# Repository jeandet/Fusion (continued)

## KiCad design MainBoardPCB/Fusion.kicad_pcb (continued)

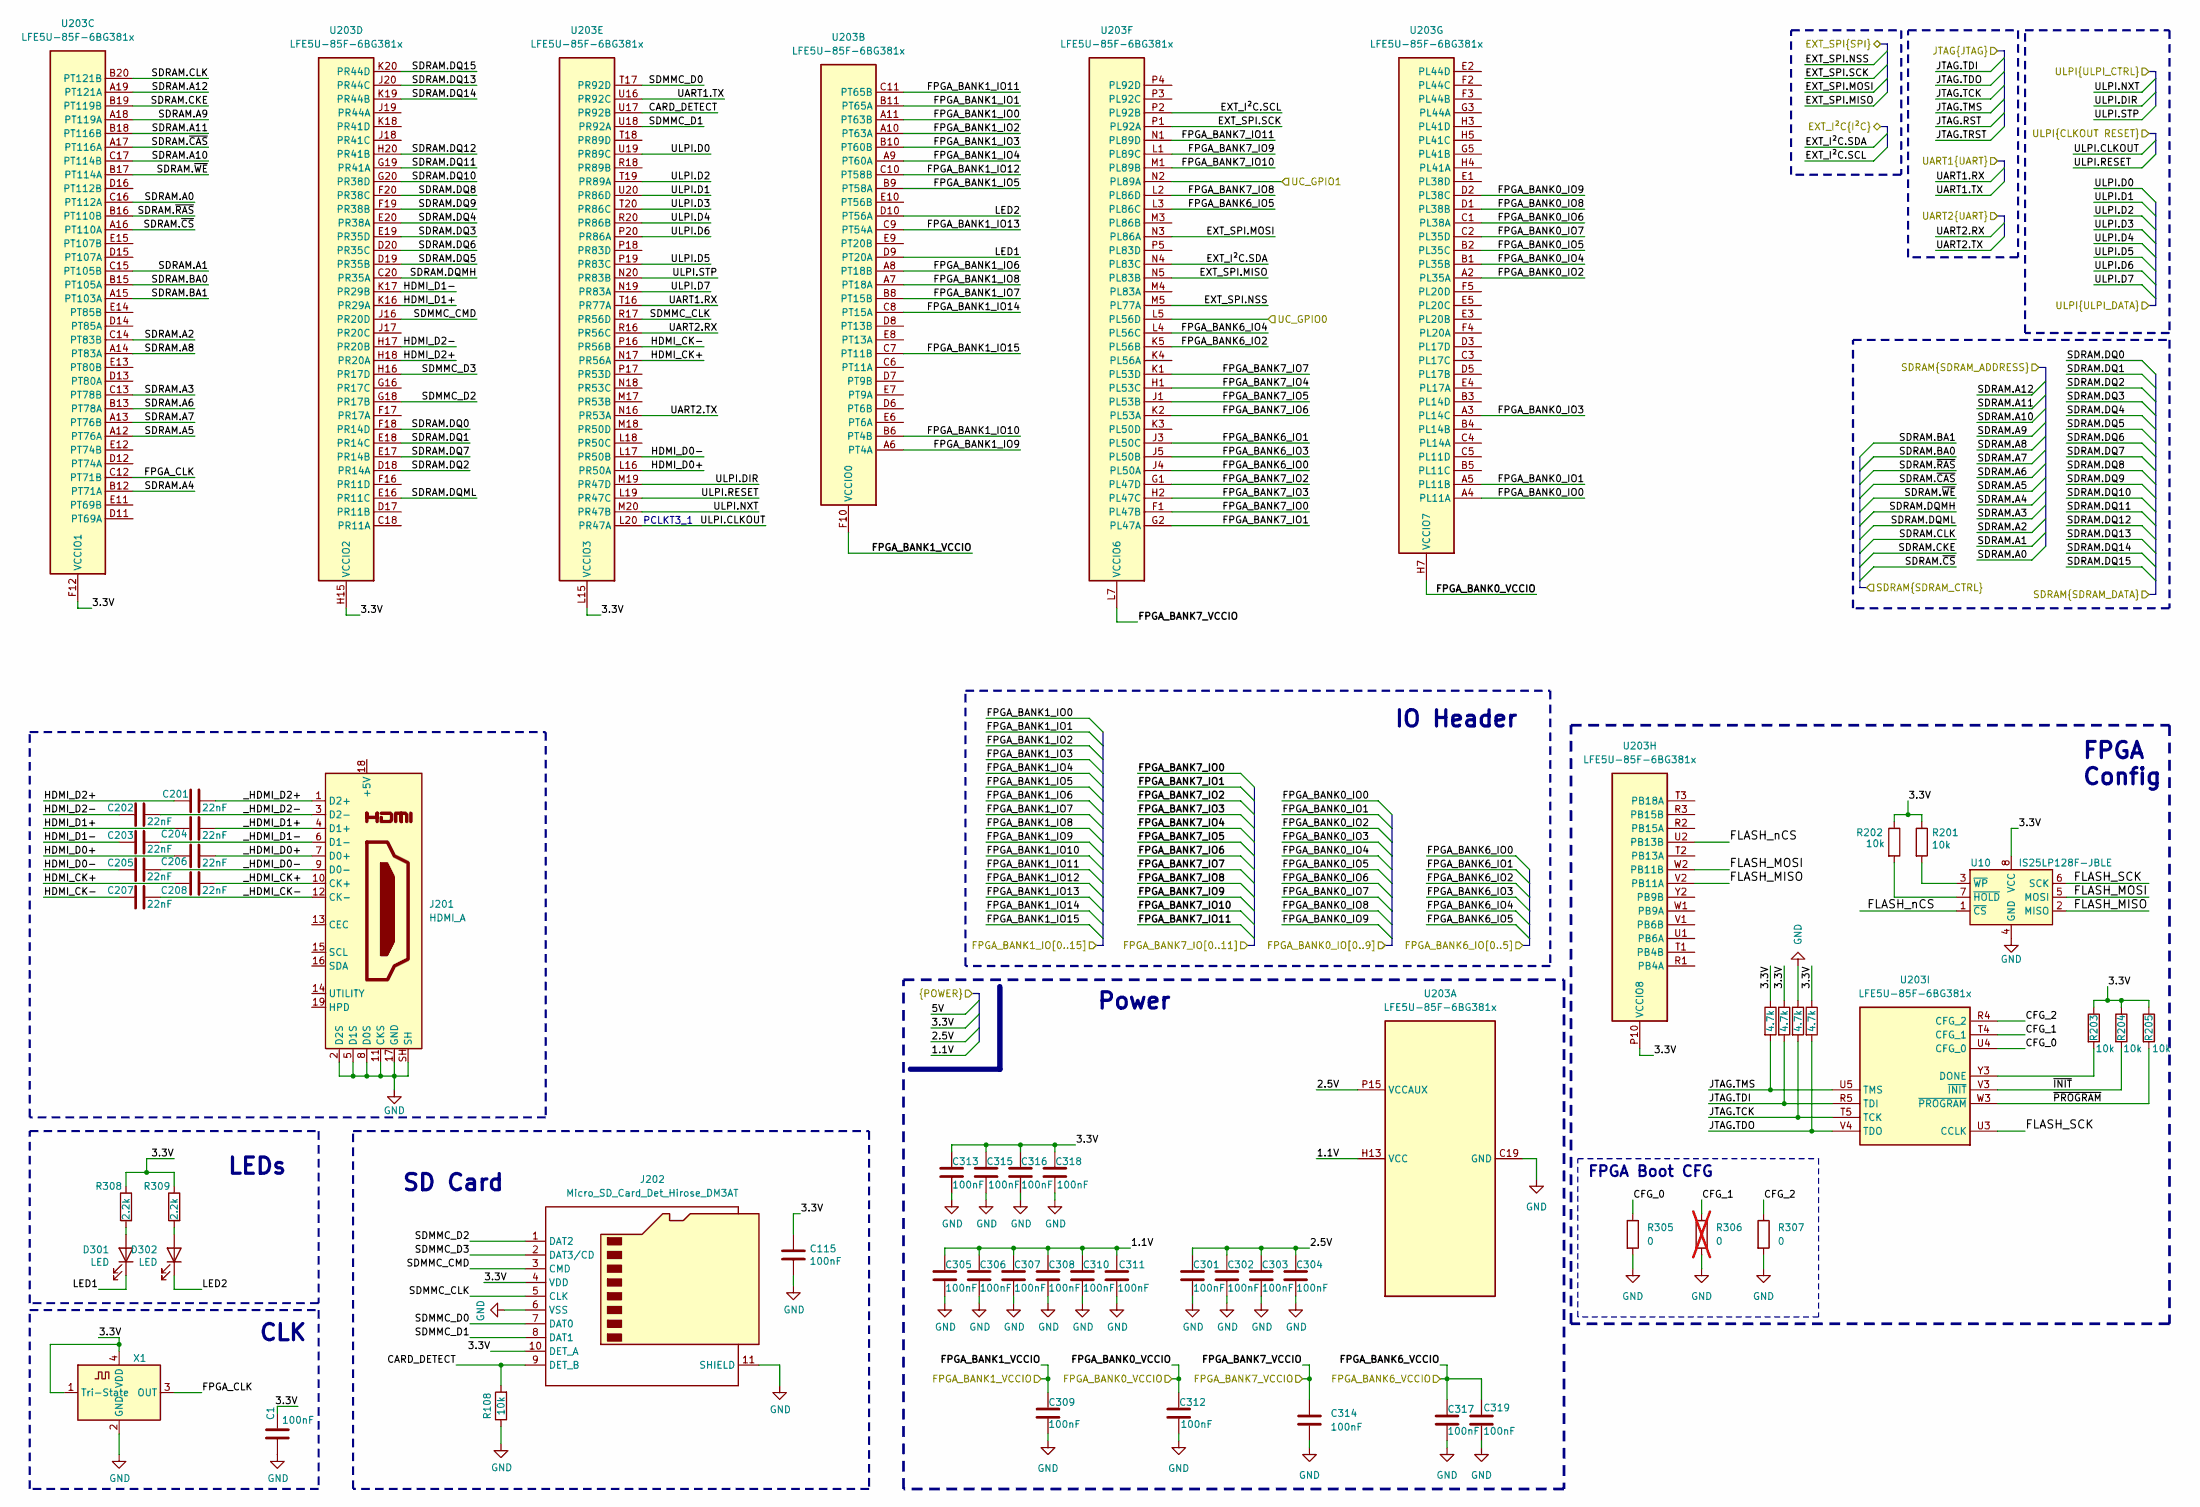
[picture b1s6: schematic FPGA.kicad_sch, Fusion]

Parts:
C1, C301, C302, C303, C304, C305, C306, C307, C308, C309, C310, C311, C312, C313, C314, C315, C316, C317, C318, C319: 100nF; C_0402_1005Metric_Pad0.74x0.62mm_HandSolder
C115: 100nF; C_0603_1608Metric_Pad1.08x0.95mm_HandSolder
C201, C202, C203, C204, C205, C206, C207, C208: 22nF; C_0402_1005Metric
D301, D302: LED; LED_0603_1608Metric_Pad1.05x0.95mm_HandSolder
J201: HDMI_A; HDMI_A_Molex_208658-1001_Horizontal
J202: Micro_SD_Card_Det_Hirose_DM3AT; microSD_HC_Hirose_DM3AT-SF-PEJM5
R108, R201, R202, R203, R204, R205: 10k; R_0402_1005Metric_Pad0.72x0.64mm_HandSolder
R301, R302, R303, R304: 4.7k; R_0402_1005Metric_Pad0.72x0.64mm_HandSolder
R305, R307: 0; R_0402_1005Metric_Pad0.72x0.64mm_HandSolder
R306: 0; R_0402_1005Metric_Pad0.72x0.64mm_HandSolder; not fitted
R308, R309: 2.2k; R_0402_1005Metric_Pad0.72x0.64mm_HandSolder
U10: IS25LP128F-JBLE; SOIC-8_5.3x5.3mm_P1.27mm; MPN IS25LP128F-JBLE; Mouser 454-W25Q128JVSIMTR
U203: LFE5U-85F-6BG381x; Lattice_caBGA-381_17x17mm_Layout20x20_P0.8mm
X1: ECS-2520MV-xxx-xx; Oscillator_SMD_ECS_2520MV-xxx-xx-4Pin_2.5x2.0mm

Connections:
/EXT_SPI_MISO: U203.N5 (PL83B); also elsewhere on the board
/EXT_SPI_MOSI: U203.N3 (PL86A); also elsewhere on the board
/EXT_SPI_NSS: U203.M5 (PL77A); also elsewhere on the board
/EXT_SPI_SCK: U203.P1 (PL92A); also elsewhere on the board
/FPGA/1.1V: C305.1, C306.1, C307.1, C308.1, C310.1, C311.1, U203.H8 (VCC), U203.H9 (VCC), U203.H10 (VCC), U203.H11 (VCC), U203.H12 (VCC), U203.H13 (VCC), U203.J8 (VCC), U203.J13 (VCC), U203.K8 (VCC), U203.K13 (VCC), U203.L8 (VCC), U203.L13 (VCC), U203.M8 (VCC), U203.M13 (VCC), U203.N8 (VCC), U203.N9 (VCC), U203.N10 (VCC), U203.N11 (VCC), U203.N12 (VCC), U203.N13 (VCC); also elsewhere on the board
/FPGA/2.5V: C301.1, C302.1, C303.1, C304.1, U203.F6 (VCCAUX), U203.F15 (VCCAUX), U203.P6 (VCCAUX), U203.P15 (VCCAUX); also elsewhere on the board
/FPGA/3.3V: C1.1, C115.1, C313.1, C315.1, C316.1, C317.1, C318.1, C319.1, J202.4 (VDD), J202.10 (DET_A), R201.1, R202.1, R203.1, R204.1, R205.1, R301.1, R303.1, R304.1, R308.1, R309.1, U10.8 (VCC), U203.F11 (VCCIO1), U203.F12 (VCCIO1), U203.H14 (VCCIO2), U203.H15 (VCCIO2), U203.J15 (VCCIO2), U203.L14 (VCCIO3), U203.L15 (VCCIO3), U203.M15 (VCCIO3), U203.P9 (VCCIO8), U203.P10 (VCCIO8), X1.1 (Tri-State), X1.4 (VDD); also elsewhere on the board
/FPGA/CARD_DETECT: J202.9 (DET_B), R108.2, U203.U17 (PR92B)
/FPGA/CFG_0: R305.1, U203.U4 (CFG_0)
/FPGA/CFG_1: R306.1, U203.T4 (CFG_1)
/FPGA/CFG_2: R307.1, U203.R4 (CFG_2)
/FPGA/FLASH_MISO: U10.2 (MISO), U203.V2 (PB11A)
/FPGA/FLASH_MOSI: U10.5 (MOSI), U203.W2 (PB11B)
/FPGA/FLASH_SCK: U10.6 (SCK), U203.U3 (CCLK)
/FPGA/FLASH_nCS: U10.1 (~CS), U203.U2 (PB13B)
/FPGA/FPGA_CLK: U203.C12 (PT71B), X1.3 (OUT)
/FPGA/HDMI_CK+: C208.1, U203.N17 (PR56A)
/FPGA/HDMI_CK-: C207.1, U203.P16 (PR56B)
/FPGA/HDMI_D0+: C206.1, U203.L16 (PR50A)
/FPGA/HDMI_D0-: C205.1, U203.L17 (PR50B)
/FPGA/HDMI_D1+: C204.1, U203.K16 (PR29A)
/FPGA/HDMI_D1-: C203.1, U203.K17 (PR29B)
/FPGA/HDMI_D2+: C201.1, U203.H18 (PR20A)
/FPGA/HDMI_D2-: C202.1, U203.H17 (PR20B)
/FPGA/JTAG.TCK: R302.2, U203.T5 (TCK); also elsewhere on the board
/FPGA/JTAG.TDI: R303.2, U203.R5 (TDI); also elsewhere on the board
/FPGA/JTAG.TDO: R301.2, U203.V4 (TDO); also elsewhere on the board
/FPGA/JTAG.TMS: R304.2, U203.U5 (TMS); also elsewhere on the board
/FPGA/LED1: D301.1 (K), U203.D9 (PT20A)
/FPGA/LED2: D302.1 (K), U203.D10 (PT56A)
/FPGA/SDMMC_CLK: J202.5 (CLK), U203.R17 (PR56D)
/FPGA/SDMMC_CMD: J202.3 (CMD), U203.J16 (PR20D)
/FPGA/SDMMC_D0: J202.7 (DAT0), U203.T17 (PR92D)
/FPGA/SDMMC_D1: J202.8 (DAT1), U203.U18 (PR92A)
/FPGA/SDMMC_D2: J202.1 (DAT2), U203.G18 (PR17B)
/FPGA/SDMMC_D3: J202.2 (DAT3/CD), U203.H16 (PR17D)
/FPGA/SDRAM.A0: U203.C16 (PT112A); also elsewhere on the board
/FPGA/SDRAM.A1: U203.C15 (PT105B); also elsewhere on the board
/FPGA/SDRAM.A2: U203.C14 (PT83B); also elsewhere on the board
/FPGA/SDRAM.A3: U203.C13 (PT78B); also elsewhere on the board
/FPGA/SDRAM.A4: U203.B12 (PT71A); also elsewhere on the board
/FPGA/SDRAM.A5: U203.A12 (PT76A); also elsewhere on the board
/FPGA/SDRAM.A6: U203.B13 (PT78A); also elsewhere on the board
/FPGA/SDRAM.A7: U203.A13 (PT76B); also elsewhere on the board
/FPGA/SDRAM.A8: U203.A14 (PT83A); also elsewhere on the board
/FPGA/SDRAM.A9: U203.A18 (PT119A); also elsewhere on the board
/FPGA/SDRAM.A10: U203.C17 (PT114B); also elsewhere on the board
/FPGA/SDRAM.A11: U203.B18 (PT116B); also elsewhere on the board
/FPGA/SDRAM.A12: U203.A19 (PT121A); also elsewhere on the board
/FPGA/SDRAM.BA0: U203.B15 (PT105A); also elsewhere on the board
/FPGA/SDRAM.BA1: U203.A15 (PT103A); also elsewhere on the board
/FPGA/SDRAM.CKE: U203.B19 (PT119B); also elsewhere on the board
/FPGA/SDRAM.CLK: U203.B20 (PT121B); also elsewhere on the board
/FPGA/SDRAM.DQ0: U203.F18 (PR14D); also elsewhere on the board
/FPGA/SDRAM.DQ1: U203.E18 (PR14C); also elsewhere on the board
/FPGA/SDRAM.DQ2: U203.D18 (PR14A); also elsewhere on the board
/FPGA/SDRAM.DQ3: U203.E19 (PR35D); also elsewhere on the board
/FPGA/SDRAM.DQ4: U203.E20 (PR38A); also elsewhere on the board
/FPGA/SDRAM.DQ5: U203.D19 (PR35B); also elsewhere on the board
/FPGA/SDRAM.DQ6: U203.D20 (PR35C); also elsewhere on the board
/FPGA/SDRAM.DQ7: U203.E17 (PR14B); also elsewhere on the board
/FPGA/SDRAM.DQ8: U203.F20 (PR38C); also elsewhere on the board
/FPGA/SDRAM.DQ9: U203.F19 (PR38B); also elsewhere on the board
/FPGA/SDRAM.DQ10: U203.G20 (PR38D); also elsewhere on the board
/FPGA/SDRAM.DQ11: U203.G19 (PR41A); also elsewhere on the board
/FPGA/SDRAM.DQ12: U203.H20 (PR41B); also elsewhere on the board
/FPGA/SDRAM.DQ13: U203.J20 (PR44C); also elsewhere on the board
/FPGA/SDRAM.DQ14: U203.K19 (PR44B); also elsewhere on the board
/FPGA/SDRAM.DQ15: U203.K20 (PR44D); also elsewhere on the board
/FPGA/SDRAM.DQMH: U203.C20 (PR35A); also elsewhere on the board
/FPGA/SDRAM.DQML: U203.E16 (PR11C); also elsewhere on the board
/FPGA/SDRAM.~CAS: U203.A17 (PT116A); also elsewhere on the board
/FPGA/SDRAM.~CS: U203.A16 (PT110A); also elsewhere on the board
/FPGA/SDRAM.~RAS: U203.B16 (PT110B); also elsewhere on the board
/FPGA/SDRAM.~WE: U203.B17 (PT114A); also elsewhere on the board
/FPGA/UART1.RX: U203.T16 (PR77A); also elsewhere on the board
/FPGA/UART1.TX: U203.U16 (PR92C); also elsewhere on the board
/FPGA/UART2.RX: U203.R16 (PR56C); also elsewhere on the board
/FPGA/UART2.TX: U203.N16 (PR53A); also elsewhere on the board
/FPGA/ULPI.CLKOUT: U203.L20 (PR47A); also elsewhere on the board
/FPGA/ULPI.D0: U203.U19 (PR89C); also elsewhere on the board
/FPGA/ULPI.D1: U203.U20 (PR86D); also elsewhere on the board
/FPGA/ULPI.D2: U203.T19 (PR89A); also elsewhere on the board
/FPGA/ULPI.D3: U203.T20 (PR86C); also elsewhere on the board
/FPGA/ULPI.D4: U203.R20 (PR86B); also elsewhere on the board
/FPGA/ULPI.D5: U203.P19 (PR83C); also elsewhere on the board
/FPGA/ULPI.D6: U203.P20 (PR86A); also elsewhere on the board
/FPGA/ULPI.D7: U203.N19 (PR83A); also elsewhere on the board
/FPGA/ULPI.DIR: U203.M19 (PR47D); also elsewhere on the board
/FPGA/ULPI.NXT: U203.M20 (PR47B); also elsewhere on the board
/FPGA/ULPI.RESET: U203.L19 (PR47C); also elsewhere on the board
/FPGA/ULPI.STP: U203.N20 (PR83B); also elsewhere on the board
/FPGA/_HDMI_CK+: C208.2, J201.10 (CK+)
/FPGA/_HDMI_CK-: C207.2, J201.12 (CK-)
/FPGA/_HDMI_D0+: C206.2, J201.7 (D0+)
/FPGA/_HDMI_D0-: C205.2, J201.9 (D0-)
/FPGA/_HDMI_D1+: C204.2, J201.4 (D1+)
/FPGA/_HDMI_D1-: C203.2, J201.6 (D1-)
/FPGA/_HDMI_D2+: C201.2, J201.1 (D2+)
/FPGA/_HDMI_D2-: C202.2, J201.3 (D2-)
/FPGA/~INIT: R204.2, U203.V3 (~INIT)
/FPGA/~PROGRAM: R205.2, U203.W3 (~PROGRAM)
/FPGA_BANK0_IO0: U203.A4 (PL11A); also elsewhere on the board
/FPGA_BANK0_IO1: U203.A5 (PL11B); also elsewhere on the board
/FPGA_BANK0_IO2: U203.A2 (PL35A); also elsewhere on the board
/FPGA_BANK0_IO3: U203.A3 (PL14C); also elsewhere on the board
/FPGA_BANK0_IO4: U203.B1 (PL35B); also elsewhere on the board
/FPGA_BANK0_IO5: U203.B2 (PL35C); also elsewhere on the board
/FPGA_BANK0_IO6: U203.C1 (PL38A); also elsewhere on the board
/FPGA_BANK0_IO7: U203.C2 (PL35D); also elsewhere on the board
/FPGA_BANK0_IO8: U203.D1 (PL38B); also elsewhere on the board
/FPGA_BANK0_IO9: U203.D2 (PL38C); also elsewhere on the board
/FPGA_BANK0_VCCIO: C312.1, U203.H6 (VCCIO7), U203.H7 (VCCIO7), U203.J6 (VCCIO7); also elsewhere on the board
/FPGA_BANK1_IO0: U203.A11 (PT63B); also elsewhere on the board
/FPGA_BANK1_IO1: U203.B11 (PT65A); also elsewhere on the board
/FPGA_BANK1_IO2: U203.A10 (PT63A); also elsewhere on the board
/FPGA_BANK1_IO3: U203.B10 (PT60B); also elsewhere on the board
/FPGA_BANK1_IO4: U203.A9 (PT60A); also elsewhere on the board
/FPGA_BANK1_IO5: U203.B9 (PT58A); also elsewhere on the board
/FPGA_BANK1_IO6: U203.A8 (PT18B); also elsewhere on the board
/FPGA_BANK1_IO7: U203.B8 (PT15B); also elsewhere on the board
/FPGA_BANK1_IO8: U203.A7 (PT18A); also elsewhere on the board
/FPGA_BANK1_IO9: U203.A6 (PT4A); also elsewhere on the board
/FPGA_BANK1_IO10: U203.B6 (PT4B); also elsewhere on the board
/FPGA_BANK1_IO11: U203.C11 (PT65B); also elsewhere on the board
/FPGA_BANK1_IO12: U203.C10 (PT58B); also elsewhere on the board
/FPGA_BANK1_IO13: U203.C9 (PT54A); also elsewhere on the board
/FPGA_BANK1_IO14: U203.C8 (PT15A); also elsewhere on the board
/FPGA_BANK1_IO15: U203.C7 (PT11B); also elsewhere on the board
/FPGA_BANK1_VCCIO: C309.1, U203.F9 (VCCIO0), U203.F10 (VCCIO0); also elsewhere on the board
/FPGA_BANK6_IO0: U203.J4 (PL50A); also elsewhere on the board
/FPGA_BANK6_IO1: U203.J3 (PL50C); also elsewhere on the board
/FPGA_BANK6_IO2: U203.K5 (PL56B); also elsewhere on the board
/FPGA_BANK6_IO3: U203.J5 (PL50B); also elsewhere on the board
/FPGA_BANK6_IO4: U203.L4 (PL56C); also elsewhere on the board
/FPGA_BANK6_IO5: U203.L3 (PL86C); also elsewhere on the board
/FPGA_BANK7_IO0: U203.F1 (PL47B); also elsewhere on the board
/FPGA_BANK7_IO1: U203.G2 (PL47A); also elsewhere on the board
/FPGA_BANK7_IO2: U203.G1 (PL47D); also elsewhere on the board
/FPGA_BANK7_IO3: U203.H2 (PL47C); also elsewhere on the board
/FPGA_BANK7_IO4: U203.H1 (PL53C); also elsewhere on the board
/FPGA_BANK7_IO5: U203.J1 (PL53B); also elsewhere on the board
/FPGA_BANK7_IO6: U203.K2 (PL53A); also elsewhere on the board
/FPGA_BANK7_IO7: U203.K1 (PL53D); also elsewhere on the board
/FPGA_BANK7_IO8: U203.L2 (PL86D); also elsewhere on the board
/FPGA_BANK7_IO9: U203.L1 (PL89C); also elsewhere on the board
/FPGA_BANK7_IO10: U203.M1 (PL89B); also elsewhere on the board
/FPGA_BANK7_IO11: U203.N1 (PL89D); also elsewhere on the board
/FPGA_BANK7_VCCIO: C314.1, U203.L6 (VCCIO6), U203.L7 (VCCIO6), U203.M6 (VCCIO6); also elsewhere on the board
/I2C1_SCL: U203.P2 (PL92B); also elsewhere on the board
/I2C1_SDA: U203.N4 (PL83C); also elsewhere on the board
/UC_GPIO0: U203.L5 (PL56D); also elsewhere on the board
/UC_GPIO1: U203.N2 (PL89A); also elsewhere on the board
GND: C1.2, C115.2, C301.2, C302.2, C303.2, C304.2, C305.2, C306.2, C307.2, C308.2, C309.2, C310.2, C311.2, C312.2, C313.2, C314.2, C315.2, C316.2, C317.2, C318.2, C319.2, J201.2 (D2S), J201.5 (D1S), J201.8 (D0S), J201.11 (CKS), J201.17 (GND), J201.SH, J202.6 (VSS), J202.11 (SHIELD), R108.1, R302.1, R305.2, R306.2, R307.2, U10.4 (GND), U203.B7 (GND), U203.B14 (GND), U203.C19 (GND), U203.D4 (GND), U203.F7 (GND), U203.F8 (GND), U203.F13 (GND), U203.F14 (GND), U203.G4 (GND), U203.G6 (GND), U203.G7 (GND), U203.G8 (GND), U203.G9 (GND), U203.G10 (GND), U203.G11 (GND), U203.G12 (GND), U203.G13 (GND), U203.G14 (GND), U203.G15 (GND), U203.G17 (GND), U203.H19 (GND), U203.J2 (GND), U203.J7 (GND), U203.J9 (GND), U203.J10 (GND), U203.J11 (GND), U203.J12 (GND), U203.J14 (GND), U203.K6 (GND), U203.K7 (GND), U203.K9 (GND), U203.K10 (GND), U203.K11 (GND), U203.K12 (GND), U203.K14 (GND), U203.K15 (GND), U203.L9 (GND), U203.L10 (GND), U203.L11 (GND), U203.L12 (GND), U203.M2 (GND), U203.M7 (GND), U203.M9 (GND), U203.M10 (GND), U203.M11 (GND), U203.M12 (GND), U203.M14 (GND), U203.M16 (GND), U203.N6 (GND), U203.N7 (GND), U203.N14 (GND), U203.N15 (GND), U203.P7 (GND), U203.P8 (GND), U203.P11 (GND), U203.P12 (GND), U203.P13 (GND), U203.P14 (GND), U203.R19 (GND), U203.T6 (GND), U203.T7 (GND), U203.T8 (GND), U203.T9 (GND), U203.T10 (GND), U203.T11 (GND), U203.T12 (GND), U203.T13 (GND), U203.T14 (GND), U203.T15 (GND), U203.U6 (GND), U203.U7 (GND), U203.U8 (GND), U203.U9 (GND), U203.U10 (GND), U203.U11 (GND), U203.U12 (GND), U203.U13 (GND), U203.U14 (GND), U203.U15 (GND), U203.V5 (GND), U203.V6 (GND), U203.V7 (GND), U203.V8 (GND), U203.V9 (GND), U203.V10 (GND), U203.V11 (GND), U203.V12 (GND), U203.V13 (GND), U203.V14 (GND), U203.V15 (GND), U203.V16 (GND), U203.V17 (GND), U203.V18 (GND), U203.V19 (GND), U203.V20 (GND), U203.W6 (GND), U203.W7 (GND), U203.W12 (GND), U203.W15 (GND), U203.W16 (GND), U203.W19 (GND), U203.W20 (GND), U203.Y5 (GND), U203.Y6 (GND), U203.Y7 (GND), U203.Y8 (GND), U203.Y11 (GND), U203.Y12 (GND), U203.Y14 (GND), U203.Y15 (GND), U203.Y16 (GND), U203.Y17 (GND), U203.Y19 (GND), X1.2 (GND); also elsewhere on the board
unnamed: D301.2 (A), R308.2
unnamed: D302.2 (A), R309.2
unnamed: R202.2, U10.7 (~HOLD)
unnamed: R201.2, U10.3 (~WP)
unnamed: R203.2, U203.Y3 (DONE)

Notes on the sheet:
FPGA Config
FPGA Boot CFG
LEDs
Power
CLK
PCLKT3_1
IO Header
SD Card

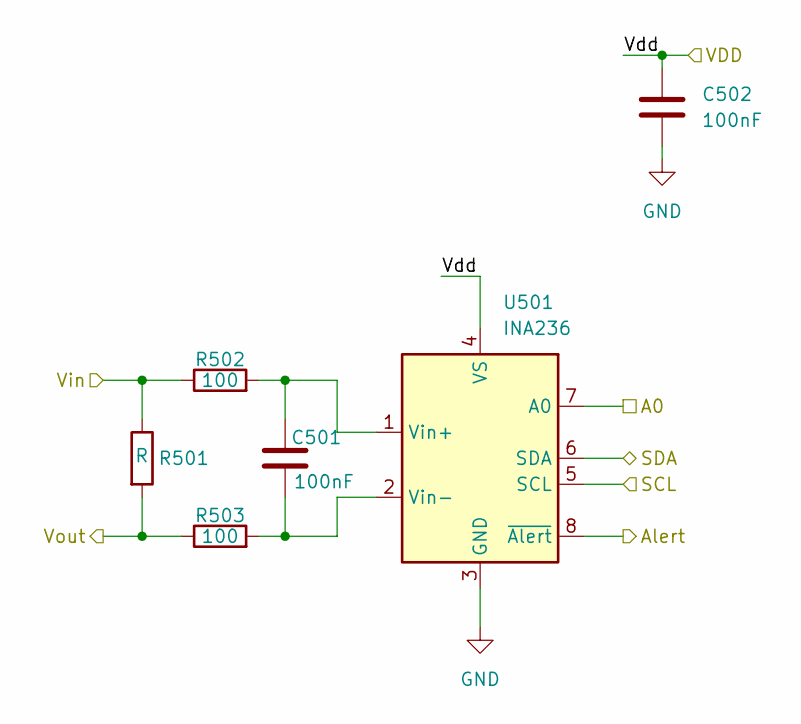
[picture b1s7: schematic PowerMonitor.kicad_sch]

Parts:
C501: 100nF; C_0402_1005Metric_Pad0.74x0.62mm_HandSolder
C502: 100nF; C_0603_1608Metric_Pad1.08x0.95mm_HandSolder
R501: R; R_1210_3225Metric_Pad1.30x2.65mm_HandSolder
R502, R503: 100; R_0402_1005Metric_Pad0.72x0.64mm_HandSolder
U501: INA236; SOT-23-8_Handsoldering

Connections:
/Alert: U501.8 (~Alert); also elsewhere on the board
/FPGA/3.3V: C502.1, R501.2, R503.1, U501.4 (VS); also elsewhere on the board
/JTAG/PSU.SCL: U501.5 (SCL); also elsewhere on the board
/JTAG/PSU.SDA: U501.6 (SDA); also elsewhere on the board
/Power/PowerMonitor1/Vin: R501.1, R502.1; also elsewhere on the board
GND: C502.2, U501.3 (GND), U501.7 (A0); also elsewhere on the board
unnamed: C501.1, R502.2, U501.1 (Vin+)
unnamed: C501.2, R503.2, U501.2 (Vin-)

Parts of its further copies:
C801, C901, C1001: 100nF; C_0402_1005Metric_Pad0.74x0.62mm_HandSolder
C802, C902, C1002: 100nF; C_0603_1608Metric_Pad1.08x0.95mm_HandSolder
R801, R901, R1001: R; R_1210_3225Metric_Pad1.30x2.65mm_HandSolder
R802, R803, R902, R903, R1002, R1003: 100; R_0402_1005Metric_Pad0.72x0.64mm_HandSolder
U801, U901, U1001: INA236; SOT-23-8_Handsoldering

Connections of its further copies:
/Alert: U801.8 (~Alert), U901.8 (~Alert), U1001.8 (~Alert); also elsewhere on the board
/FPGA/1.1V: R801.2, R803.1; also elsewhere on the board
/FPGA/2.5V: R901.2, R903.1; also elsewhere on the board
/FPGA/3.3V: C802.1, C902.1, C1002.1, U801.4 (VS), U801.7 (A0), U901.4 (VS), U1001.4 (VS); also elsewhere on the board
/FPGA/5V: R1001.2, R1003.1; also elsewhere on the board
/JTAG/PSU.SCL: U801.5 (SCL), U901.5 (SCL), U1001.5 (SCL), U1001.7 (A0); also elsewhere on the board
/JTAG/PSU.SDA: U801.6 (SDA), U901.6 (SDA), U901.7 (A0), U1001.6 (SDA); also elsewhere on the board
/Power/PowerMonitor2/Vin: R901.1, R902.1; also elsewhere on the board
/Power/PowerMonitor/Vin: R801.1, R802.1; also elsewhere on the board
/USB_5V: R1001.1, R1002.1; also elsewhere on the board
GND: C802.2, C902.2, C1002.2, U801.3 (GND), U901.3 (GND), U1001.3 (GND); also elsewhere on the board
unnamed: C801.1, R802.2, U801.1 (Vin+)
unnamed: C801.2, R803.2, U801.2 (Vin-)
unnamed: C901.1, R902.2, U901.1 (Vin+)
unnamed: C901.2, R903.2, U901.2 (Vin-)
unnamed: C1001.1, R1002.2, U1001.1 (Vin+)
unnamed: C1001.2, R1003.2, U1001.2 (Vin-)

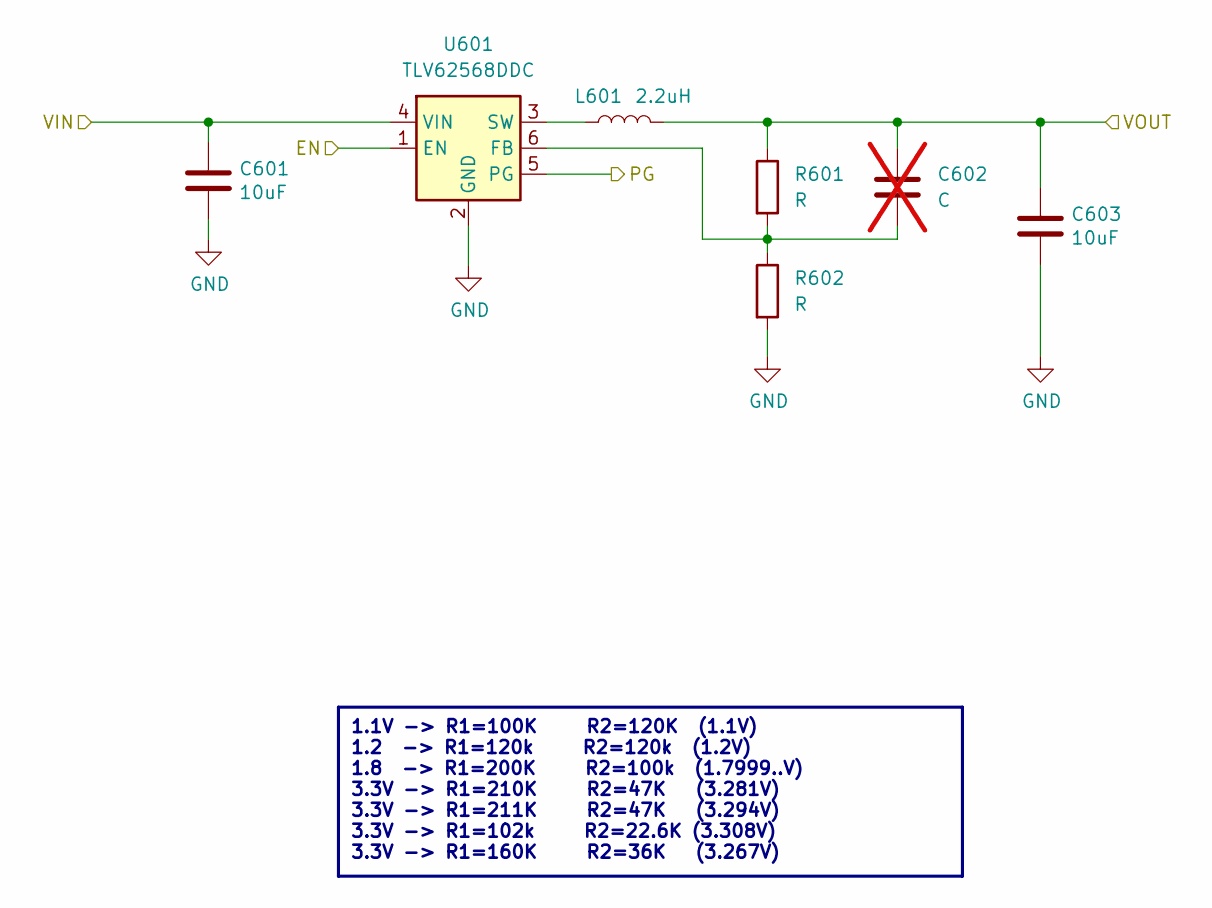
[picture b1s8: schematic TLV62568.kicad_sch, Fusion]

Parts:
C601, C603: 10uF; C_1206_3216Metric_Pad1.33x1.80mm_HandSolder
C602: C; C_0402_1005Metric_Pad0.74x0.62mm_HandSolder; not fitted
L601: 2.2uH; L_1206_3216Metric_Pad1.42x1.75mm_HandSolder
R601, R602: R; R_0402_1005Metric_Pad0.72x0.64mm_HandSolder
U601: TLV62568DDC; SOT-23-6

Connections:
/FPGA/5V: C601.1, U601.1 (EN), U601.4 (VIN); also elsewhere on the board
/Power/PowerMonitor1/Vin: C602.1, C603.1, L601.2, R601.1; also elsewhere on the board
/Power/TLV62568/PG: U601.5 (PG); also elsewhere on the board
GND: C601.2, C603.2, R602.2, U601.2 (GND); also elsewhere on the board
unnamed: C602.2, R601.2, R602.1, U601.6 (FB)
unnamed: L601.1, U601.3 (SW)

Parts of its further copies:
C701, C703: 10uF; C_1206_3216Metric_Pad1.33x1.80mm_HandSolder
C702: C; C_0402_1005Metric_Pad0.74x0.62mm_HandSolder; not fitted
L701: 2.2uH; L_1206_3216Metric_Pad1.42x1.75mm_HandSolder
R701, R702: R; R_0402_1005Metric_Pad0.72x0.64mm_HandSolder
U701: TLV62568DDC; SOT-23-6

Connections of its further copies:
/FPGA/5V: C701.1, U701.4 (VIN); also elsewhere on the board
/Power/PowerMonitor/Vin: C702.1, C703.1, L701.2, R701.1; also elsewhere on the board
/Power/TLV62568/PG: U701.1 (EN); also elsewhere on the board
/Power/TLV62569/PG: U701.5 (PG)
GND: C701.2, C703.2, R702.2, U701.2 (GND); also elsewhere on the board
unnamed: C702.2, R701.2, R702.1, U701.6 (FB)
unnamed: L701.1, U701.3 (SW)

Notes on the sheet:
1.1V -> R1=100K R2=120K (1.1V) 1.2 -> R1=120k R2=120k (1.2V) 1.8 -> R1=200K R2=100k (1.7999..V) 3.3V -> R1=210K R2=47K (3.281V) 3.3V -> R1=211K R2=47K (3.294V) 3.3V -> R1=102k R2=22.6K (3.308V) 3.3V -> R1=160K R2=36K (3.267V)

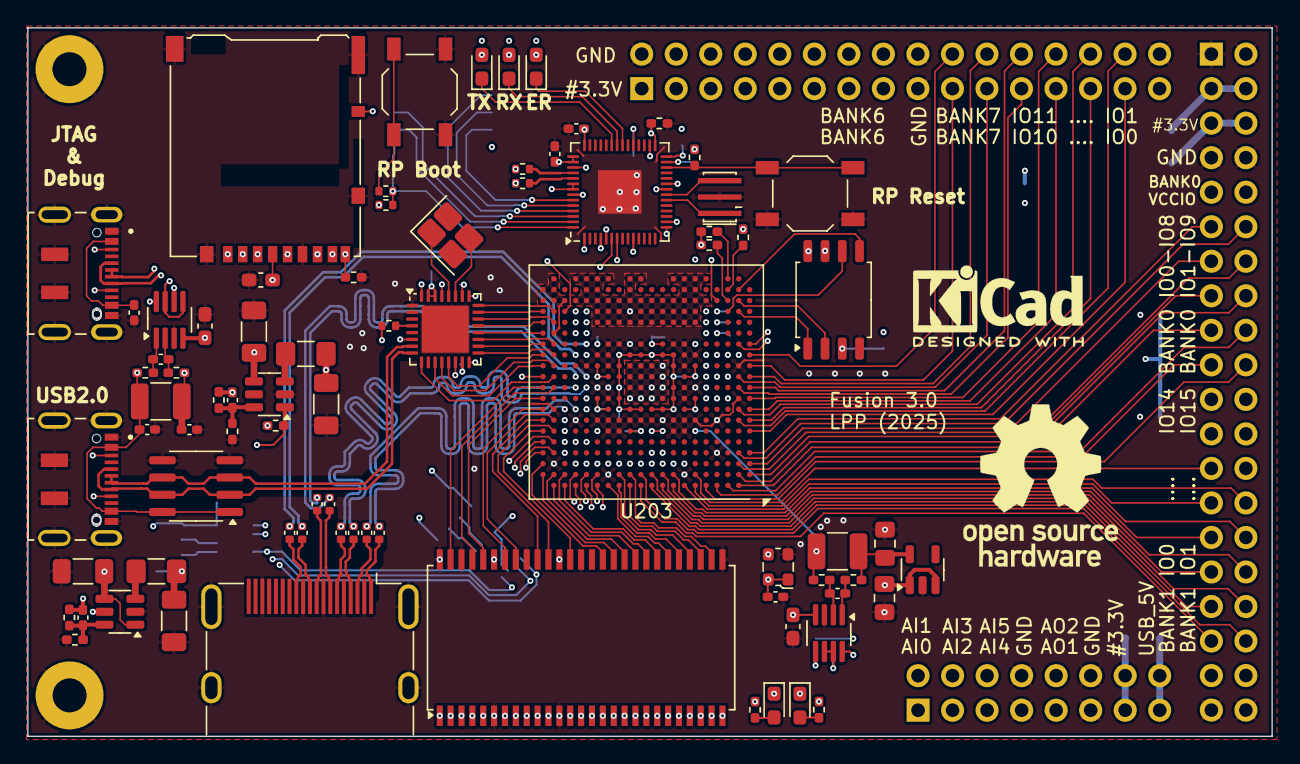
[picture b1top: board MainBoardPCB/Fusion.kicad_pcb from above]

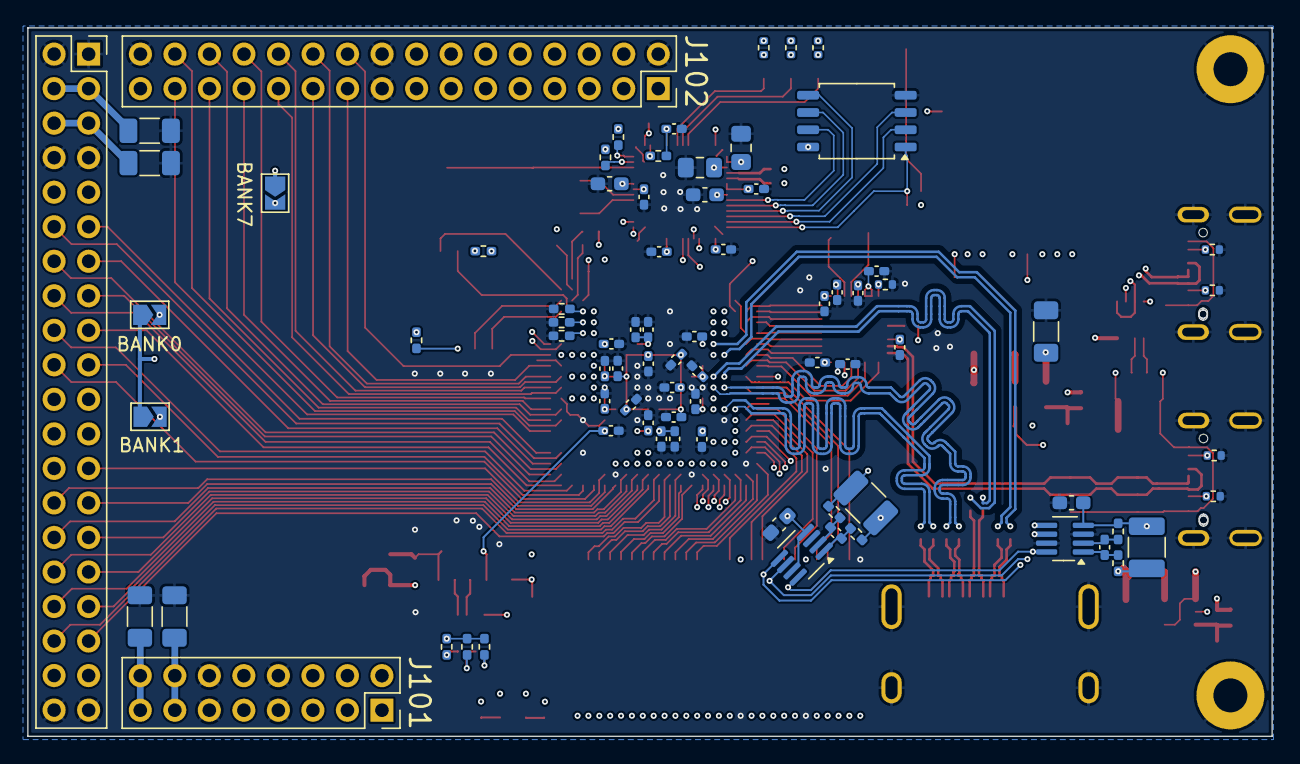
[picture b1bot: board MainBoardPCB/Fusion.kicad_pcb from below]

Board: 4 copper layers, 91.5 x 52.1 mm, 159 parts (78 on the bottom side), 214 nets.

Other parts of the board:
H101, H102: MountingHole_Pad; MountingHole_2.5mm_Pad
SYM101: Logo_Open_Hardware_Small; OSHW-Logo_11.4x12mm_SilkScreen

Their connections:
GND: H101.1, H102.1; also elsewhere on the board

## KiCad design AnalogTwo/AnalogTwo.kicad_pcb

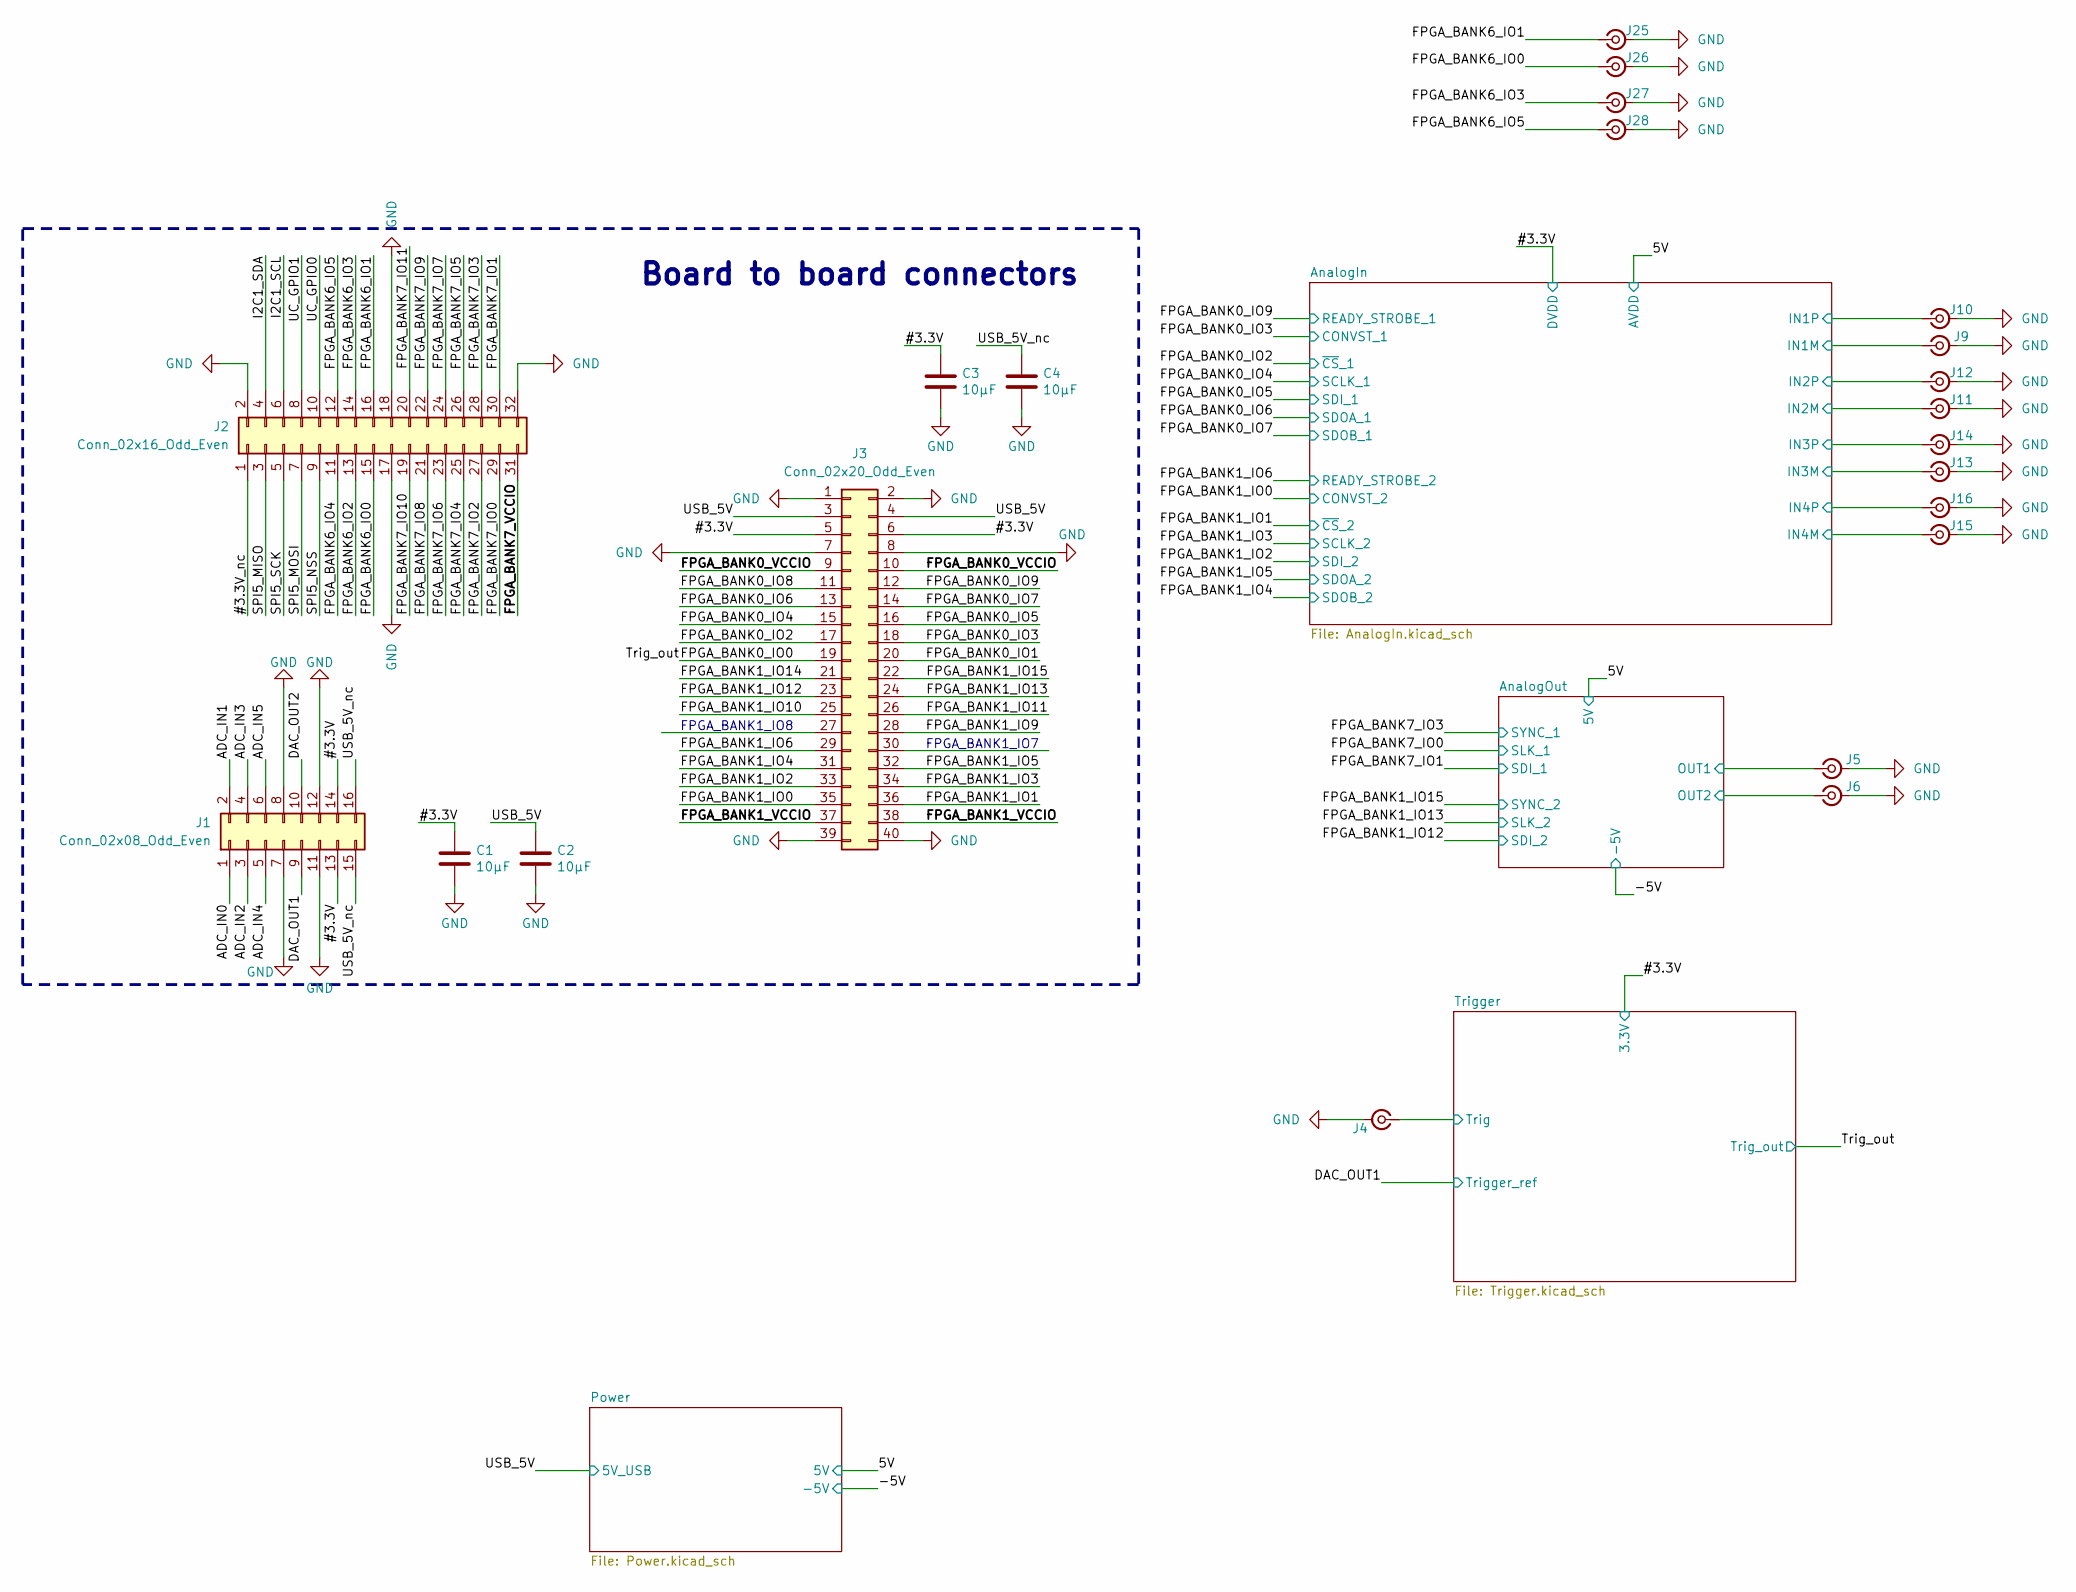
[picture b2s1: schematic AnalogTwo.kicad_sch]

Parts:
C1, C2, C3, C4: 10µF; C_0805_2012Metric_Pad1.18x1.45mm_HandSolder
J1: Conn_02x08_Odd_Even; PinSocket_2x08_P2.54mm_Vertical
J2: Conn_02x16_Odd_Even; PinSocket_2x16_P2.54mm_Vertical
J3: Conn_02x20_Odd_Even; PinSocket_2x20_P2.54mm_Vertical
J4, J5, J6, J9, J10, J11, J12, J13, J14, J15, J16, J25, J26, J27, J28: Conn_Coaxial_Small; SMB_Jack_Vertical

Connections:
/#3.3V: C1.1, C3.1, J1.13, J1.14, J3.5, J3.6; also elsewhere on the board
/#3.3V_nc: J2.1
/ADC_IN0: J1.1
/ADC_IN1: J1.2
/ADC_IN2: J1.3
/ADC_IN3: J1.4
/ADC_IN4: J1.5
/ADC_IN5: J1.6
/AnalogIn/IN1M: J9.1 (In); also elsewhere on the board
/AnalogIn/IN1P: J10.1 (In); also elsewhere on the board
/AnalogIn/IN2M: J11.1 (In); also elsewhere on the board
/AnalogIn/IN2P: J12.1 (In); also elsewhere on the board
/AnalogIn/IN3M: J13.1 (In); also elsewhere on the board
/AnalogIn/IN3P: J14.1 (In); also elsewhere on the board
/AnalogIn/IN4M: J15.1 (In); also elsewhere on the board
/AnalogIn/IN4P: J16.1 (In); also elsewhere on the board
/AnalogOut/OUT1: J5.1 (In); also elsewhere on the board
/AnalogOut/OUT2: J6.1 (In); also elsewhere on the board
/DAC_OUT1: J1.9; also elsewhere on the board
/DAC_OUT2: J1.10
/FPGA_BANK0_IO0: J3.19; also elsewhere on the board
/FPGA_BANK0_IO1: J3.20
/FPGA_BANK0_IO2: J3.17; also elsewhere on the board
/FPGA_BANK0_IO3: J3.18; also elsewhere on the board
/FPGA_BANK0_IO4: J3.15; also elsewhere on the board
/FPGA_BANK0_IO5: J3.16; also elsewhere on the board
/FPGA_BANK0_IO6: J3.13; also elsewhere on the board
/FPGA_BANK0_IO7: J3.14; also elsewhere on the board
/FPGA_BANK0_IO8: J3.11
/FPGA_BANK0_IO9: J3.12; also elsewhere on the board
/FPGA_BANK0_VCCIO: J3.9, J3.10
/FPGA_BANK1_IO0: J3.35; also elsewhere on the board
/FPGA_BANK1_IO1: J3.36; also elsewhere on the board
/FPGA_BANK1_IO2: J3.33; also elsewhere on the board
/FPGA_BANK1_IO3: J3.34; also elsewhere on the board
/FPGA_BANK1_IO4: J3.31; also elsewhere on the board
/FPGA_BANK1_IO5: J3.32; also elsewhere on the board
/FPGA_BANK1_IO6: J3.29; also elsewhere on the board
/FPGA_BANK1_IO9: J3.28
/FPGA_BANK1_IO10: J3.25
/FPGA_BANK1_IO11: J3.26
/FPGA_BANK1_IO12: J3.23; also elsewhere on the board
/FPGA_BANK1_IO13: J3.24; also elsewhere on the board
/FPGA_BANK1_IO14: J3.21
/FPGA_BANK1_IO15: J3.22; also elsewhere on the board
/FPGA_BANK1_VCCIO: J3.37, J3.38
/FPGA_BANK6_IO0: J2.15, J26.1 (In)
/FPGA_BANK6_IO1: J2.16, J25.1 (In)
/FPGA_BANK6_IO2: J2.13
/FPGA_BANK6_IO3: J2.14, J27.1 (In)
/FPGA_BANK6_IO4: J2.11
/FPGA_BANK6_IO5: J2.12, J28.1 (In)
/FPGA_BANK7_IO0: J2.29; also elsewhere on the board
/FPGA_BANK7_IO1: J2.30; also elsewhere on the board
/FPGA_BANK7_IO2: J2.27
/FPGA_BANK7_IO3: J2.28; also elsewhere on the board
/FPGA_BANK7_IO4: J2.25
/FPGA_BANK7_IO5: J2.26
/FPGA_BANK7_IO6: J2.23
/FPGA_BANK7_IO7: J2.24
/FPGA_BANK7_IO8: J2.21
/FPGA_BANK7_IO9: J2.22
/FPGA_BANK7_IO10: J2.19
/FPGA_BANK7_IO11: J2.20
/FPGA_BANK7_VCCIO: J2.31
/I2C1_SCL: J2.6
/I2C1_SDA: J2.4
/SPI5_MISO: J2.3
/SPI5_MOSI: J2.7
/SPI5_NSS: J2.9
/SPI5_SCK: J2.5
/Trigger/Trig: J4.1 (In); also elsewhere on the board
/UC_GPIO0: J2.10
/UC_GPIO1: J2.8
/USB_5V: C2.1, J3.3, J3.4; also elsewhere on the board
/USB_5V_nc: C4.1, J1.15, J1.16
GND: C1.2, C2.2, C3.2, C4.2, J1.7, J1.8, J1.11, J1.12, J2.2, J2.17, J2.18, J2.32, J3.1, J3.2, J3.7, J3.8, J3.39, J3.40, J4.2 (Ext), J5.2 (Ext), J6.2 (Ext), J9.2 (Ext), J10.2 (Ext), J11.2 (Ext), J12.2 (Ext), J13.2 (Ext), J14.2 (Ext), J15.2 (Ext), J16.2 (Ext), J25.2 (Ext), J26.2 (Ext), J27.2 (Ext), J28.2 (Ext); also elsewhere on the board

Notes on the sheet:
FPGA_BANK1_IO7
Board to board connectors
FPGA_BANK1_IO8

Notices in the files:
AnalogTwo/ADC.kicad_sch:
CC-BY-SA
